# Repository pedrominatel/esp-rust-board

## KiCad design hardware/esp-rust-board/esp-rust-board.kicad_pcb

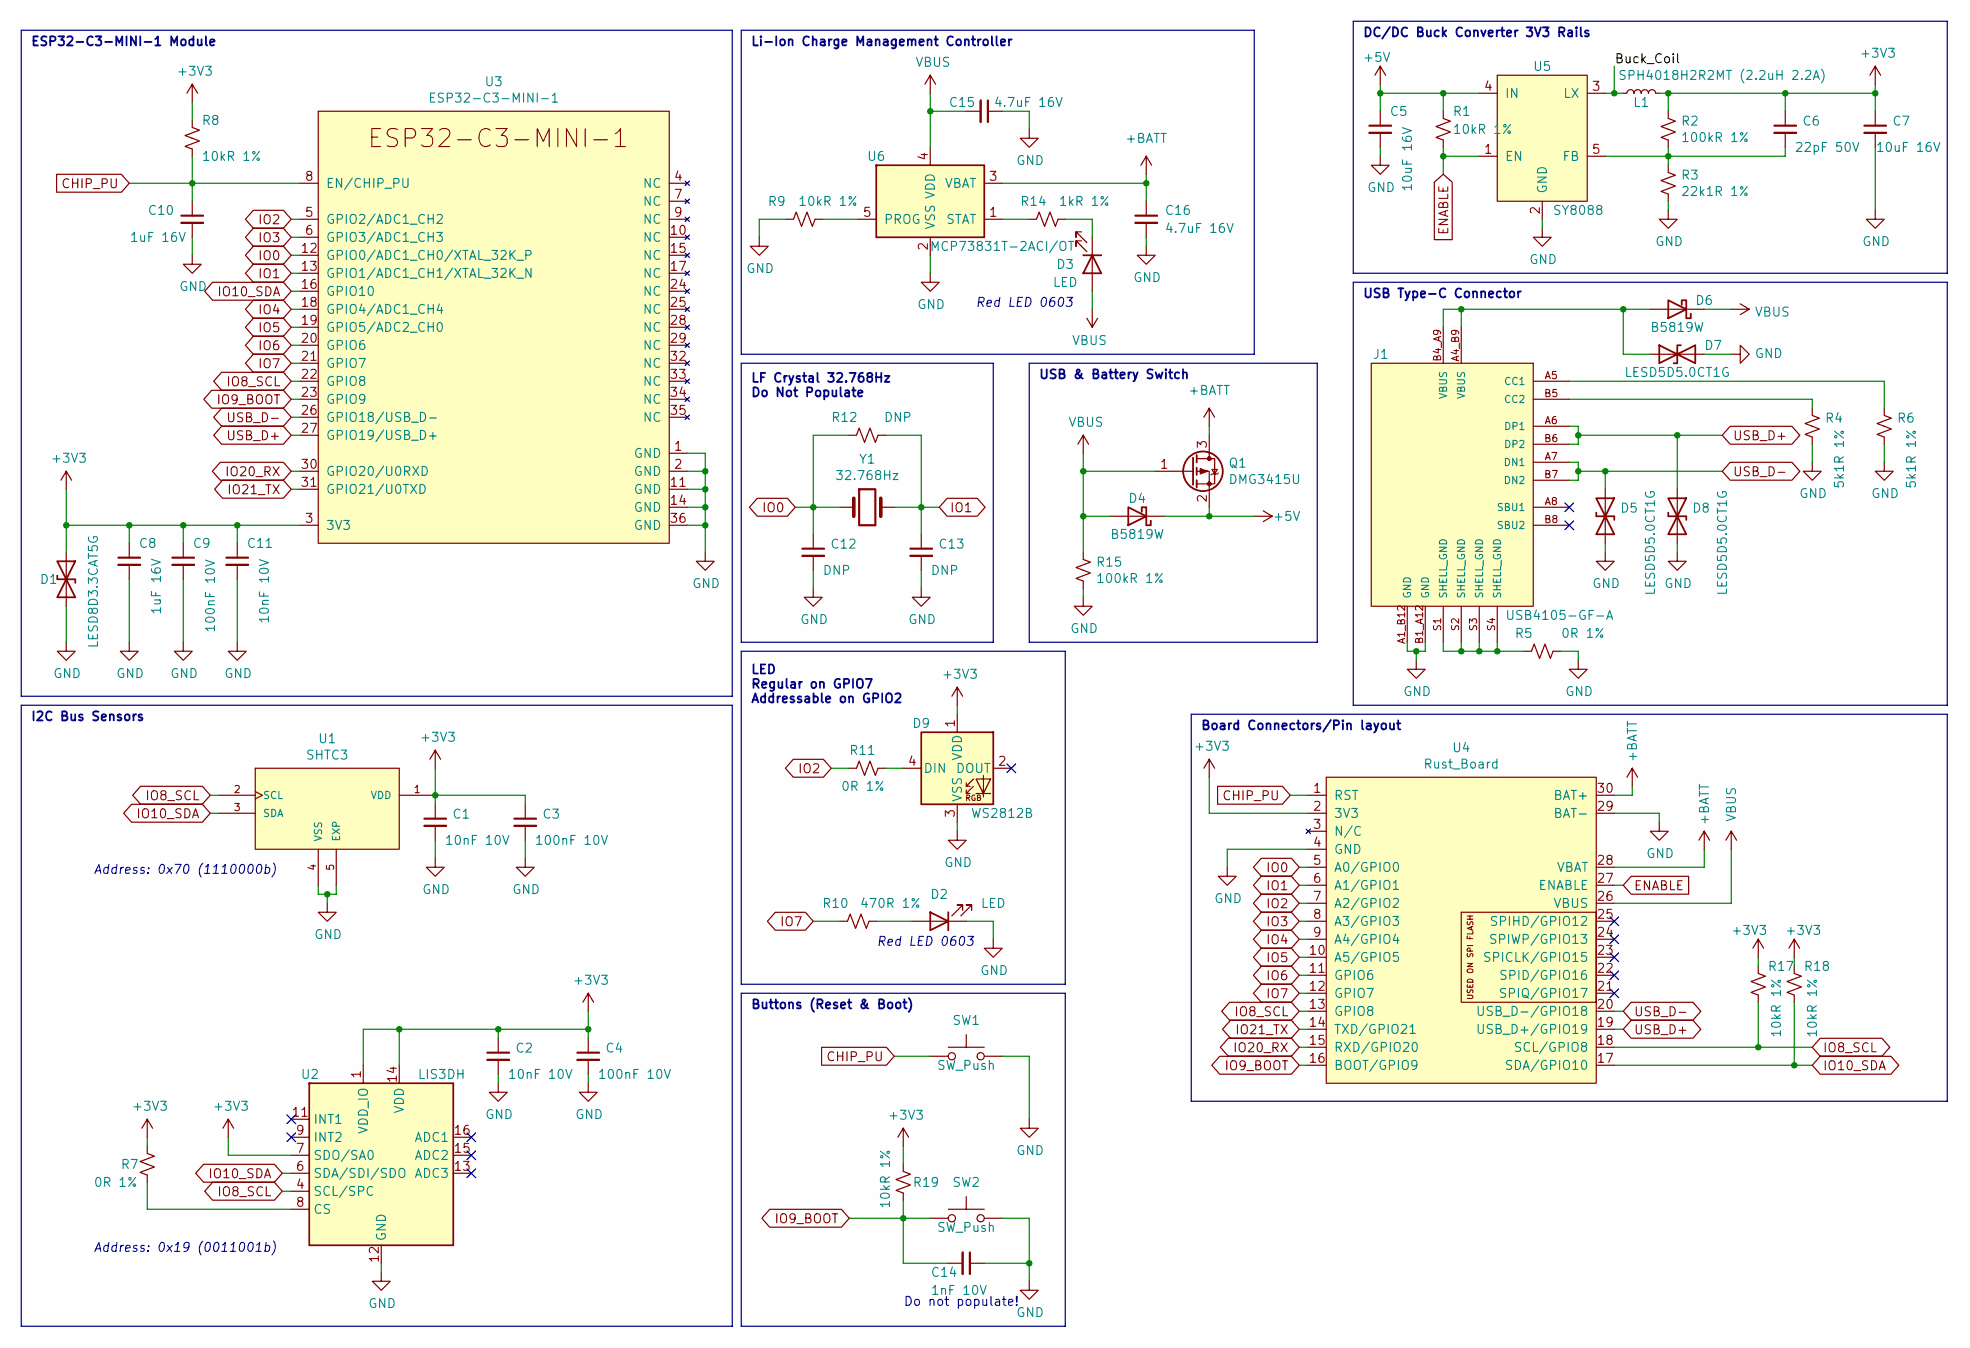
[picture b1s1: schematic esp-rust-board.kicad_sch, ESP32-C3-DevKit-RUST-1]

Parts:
C1, C2, C11: 10nF 10V; C_0402_1005Metric; LCSC C15195
C3, C4, C9: 100nF 10V; C_0402_1005Metric; LCSC C1525
C5, C7: 10uF 16V; C_0805_2012Metric; LCSC C15850
C6: 22pF 50V; C_0603_1608Metric; LCSC C1653
C8, C10: 1uF 16V; C_0402_1005Metric; LCSC C52923
C12, C13: DNP; C_0402_1005Metric
C14: 1nF 10V; C_0402_1005Metric; LCSC C1523
C15, C16: 4.7uF 16V; C_0603_1608Metric; LCSC C19666
D1: LESD8D3.3CAT5G; SOD-882; LCSC C172409
D2, D3: LED; LED_0603_1608Metric; LCSC C2286
D4, D6: B5819W; D_SOD-123; LCSC C8598
D5, D7, D8: LESD5D5.0CT1G; D_SOD-523; LCSC C383211
D9: WS2812B; LED_SK6812MINI_PLCC4_3.5x3.5mm_P1.75mm; LCSC C527089
J1: USB4105-GF-A; GCT_USB4105-GF-A; PARTREV A3; LCSC C165948
L1: SPH4018H2R2MT (2.2uH 2.2A); L_Bourns-SRN4018; LCSC C370436
Q1: DMG3415U; SOT-23; LCSC C96616
R1, R8, R9, R17, R18, R19: 10kR 1%; R_0402_1005Metric; LCSC C25744
R2, R15: 100kR 1%; R_0402_1005Metric; LCSC C25741
R3: 22k1R 1%; R_0402_1005Metric; LCSC C43473
R4, R6: 5k1R 1%; R_0402_1005Metric; LCSC C25905
R5, R7, R11: 0R 1%; R_0402_1005Metric; LCSC C17168
R10: 470R 1%; R_0402_1005Metric; LCSC C25117
R12: DNP; R_0402_1005Metric
R14: 1kR 1%; R_0402_1005Metric; LCSC C11702
SW1, SW2: SW_Push; SW_SPST_PTS810; LCSC C116501
U1: SHTC3; SON100P200X200X80-5N; PARTREV 3; LCSC C194656
U2: LIS3DH; LGA-16_3x3mm_P0.5mm_LayoutBorder3x5y; LCSC C15134
U3: ESP32-C3-MINI-1; LCSC C2838502
U4: Rust_Board
U5: SY8088; SOT-23-5; LCSC C479072
U6: MCP73831T-2ACI/OT; SOT-23-5; LCSC C424093
Y1: 32.768Hz; Crystal_SMD_3215-2Pin_3.2x1.5mm

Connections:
+3V3: C1.1, C2.1, C3.1, C4.1, C6.1, C7.1, C8.1, C9.1, C11.1, D1.1 (A1), D9.1 (VDD), L1.2, R2.1, R7.1, R8.1, R17.1, R18.1, R19.1, U1.1 (VDD), U2.1 (VDD_IO), U2.7 (SDO/SA0), U2.14 (VDD), U3.3 (3V3), U4.2 (3V3)
+5V: C5.1, D4.1 (K), Q1.2 (S), R1.1, U5.4 (IN)
+BATT: C16.1, Q1.3 (D), U4.28 (VBAT), U4.30 (BAT+), U6.3 (VBAT)
/Buck_Coil: L1.1, U5.3 (LX)
CHIP_PU: C10.1, R8.2, SW1.1, U3.8 (EN/CHIP_PU), U4.1 (RST)
ENABLE: R1.2, U4.27 (ENABLE), U5.1 (EN)
GND: C1.2, C2.2, C3.2, C4.2, C5.2, C7.2, C8.2, C9.2, C10.2, C11.2, C12.2, C13.2, C14.1, C15.1, C16.2, D1.2 (A2), D2.1 (K), D5.2 (A2), D7.2 (A2), D8.2 (A2), D9.3 (VSS), J1.A1_B12 (GND), J1.B1_A12 (GND), R3.2, R4.2, R5.2, R6.2, R9.1, R15.2, SW1.2, SW2.2, U1.4 (VSS), U1.5 (EXP), U2.5 (GND), U2.10 (GND), U2.12 (GND), U3.1 (GND), U3.2 (GND), U3.11 (GND), U3.14 (GND), U3.36 (GND), U4.4 (GND), U4.29 (BAT-), U5.2 (GND), U6.2 (VSS)
IO0: C12.1, R12.1, U3.12 (GPIO0/ADC1_CH0/XTAL_32K_P), U4.5 (A0/GPIO0), Y1.1
IO1: C13.1, R12.2, U3.13 (GPIO1/ADC1_CH1/XTAL_32K_N), U4.6 (A1/GPIO1), Y1.2
IO2: R11.1, U3.5 (GPIO2/ADC1_CH2), U4.7 (A2/GPIO2)
IO3: U3.6 (GPIO3/ADC1_CH3), U4.8 (A3/GPIO3)
IO4: U3.18 (GPIO4/ADC1_CH4), U4.9 (A4/GPIO4)
IO5: U3.19 (GPIO5/ADC2_CH0), U4.10 (A5/GPIO5)
IO6: U3.20 (GPIO6), U4.11 (GPIO6)
IO7: R10.1, U3.21 (GPIO7), U4.12 (GPIO7)
IO8_SCL: R17.2, U1.2 (SCL), U2.4 (SCL/SPC), U3.22 (GPIO8), U4.13 (GPIO8), U4.18 (SCL/GPIO8)
IO9_BOOT: C14.2, R19.2, SW2.1, U3.23 (GPIO9), U4.16 (BOOT/GPIO9)
IO10_SDA: R18.2, U1.3 (SDA), U2.6 (SDA/SDI/SDO), U3.16 (GPIO10), U4.17 (SDA/GPIO10)
IO20_RX: U3.30 (GPIO20/U0RXD), U4.15 (RXD/GPIO20)
IO21_TX: U3.31 (GPIO21/U0TXD), U4.14 (TXD/GPIO21)
unnamed: C6.2, R2.2, R3.1, U5.5 (FB)
unnamed: D2.2 (A), R10.2
unnamed: D3.1 (K), R14.2
unnamed: D6.2 (A), D7.1 (A1), J1.A4_B9 (VBUS), J1.B4_A9 (VBUS)
unnamed: D9.4 (DIN), R11.2
unnamed: J1.A5 (CC1), R6.1
unnamed: J1.B5 (CC2), R4.1
unnamed: J1.S1 (SHELL_GND), J1.S2 (SHELL_GND), J1.S3 (SHELL_GND), J1.S4 (SHELL_GND), R5.1
unnamed: R7.2, U2.8 (CS)
unnamed: R9.2, U6.5 (PROG)
unnamed: R14.1, U6.1 (STAT)
USB_D+: D8.1 (A1), J1.A6 (DP1), J1.B6 (DP2), U3.27 (GPIO19/USB_D+), U4.19 (USB_D+/GPIO19)
USB_D-: D5.1 (A1), J1.A7 (DN1), J1.B7 (DN2), U3.26 (GPIO18/USB_D-), U4.20 (USB_D-/GPIO18)
VBUS: C15.2, D3.2 (A), D4.2 (A), D6.1 (K), Q1.1 (G), R15.1, U4.26 (VBUS), U6.4 (VDD)

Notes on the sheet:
USB Type-C Connector
Do not populate!
Buttons (Reset & Boot)
Address: 0x70 (1110000b)
Red LED 0603
LF Crystal 32.768Hz Do Not Populate
DC/DC Buck Converter 3V3 Rails
USB & Battery Switch
Board Connectors/Pin layout
LED Regular on GPIO7 Addressable on GPIO2
Address: 0x19 (0011001b)
ESP32-C3-MINI-1 Module
Li-Ion Charge Management Controller
I2C Bus Sensors

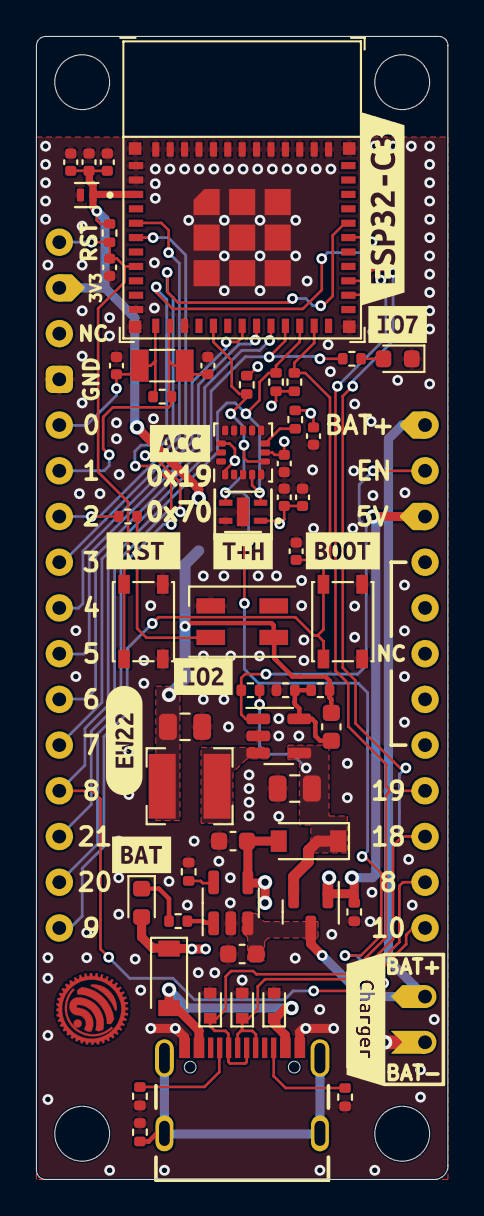
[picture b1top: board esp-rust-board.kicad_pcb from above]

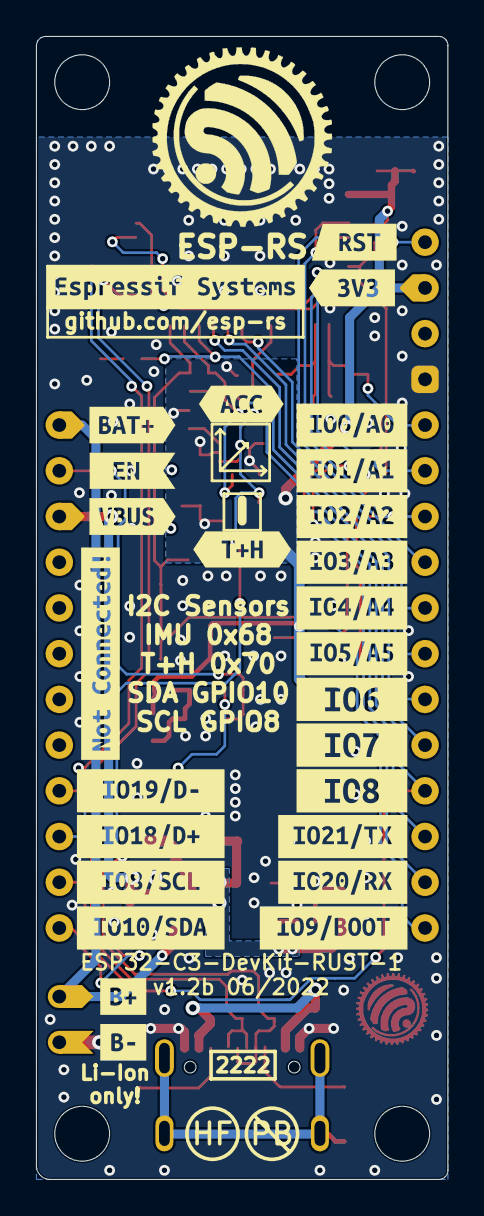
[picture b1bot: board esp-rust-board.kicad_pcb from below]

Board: 2 copper layers, 22.9 x 63.5 mm, 92 parts (27 on the bottom side), 34 nets.

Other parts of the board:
kibuzzard-61B9CE3D, kibuzzard-61B9CE86, kibuzzard-61B9CEAB, kibuzzard-61B9EF98, kibuzzard-61C0F3FF, kibuzzard-61C0F315, kibuzzard-61C0F325, kibuzzard-61C0F363, kibuzzard-61C0F406, kibuzzard-61C0F511, kibuzzard-61C0F551, kibuzzard-61C05A22, kibuzzard-61C05B60, kibuzzard-61C05BAC, kibuzzard-61C05C0D, kibuzzard-61C05C87, kibuzzard-61C05C92, kibuzzard-61C05D58, kibuzzard-61C05D75, kibuzzard-61C05DB0, kibuzzard-61C057D5, kibuzzard-61C057FD, kibuzzard-61C0588C, kibuzzard-61C0597E, kibuzzard-61C05335, kibuzzard-61C05804, kibuzzard-61C05909, kibuzzard-61C05949, kibuzzard-61C05975: G***; label
kibuzzard-61E1AB2E: G***; kibuzzard-61E1AB2E
kibuzzard-61F2685B: G***; kibuzzard-61F2685B
kibuzzard-61F26841: G***; kibuzzard-61F26841
kibuzzard-61F26855: G***; kibuzzard-61F26855
kibuzzard-623DAB98: G***; kibuzzard-623DAB98
kibuzzard-62974DD1: G***; kibuzzard-62974DD1
kibuzzard-62975A90: G***; kibuzzard-62975A90
kibuzzard-6269032F: G***; kibuzzard-6269032F
kibuzzard-6297573C: G***; kibuzzard-6297573C

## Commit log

2022-01-27 Review on the DRC warnings and labels (#27)
    * [HW] Added new schematic
    * [HW] WIP on the schematic
    * [HW] Added PCB design file and schematic in PDF file
    * [HW] Buck position changed and Rust Logo removed from schematic and PDF
    * [HW] Added new setp files for SHTC3 and updates on the PCB and schematics
    * [HW] Added images, PDF and minor fixes
2022-01-27 Gitignore update and backup files removed (#28)
    * [HW] Added new schematic
    * [HW] WIP on the schematic
    * [HW] Added PCB design file and schematic in PDF file
    * [HW] Buck position changed and Rust Logo removed from schematic and PDF
    * [HW] Added new setp files for SHTC3 and updates on the PCB and schematics
    * [HW] Added images, PDF and minor fixes
2022-01-27 Removed backup files and fabrication zip file
2022-06-01 Added LIS3DH
2022-06-14 Sync
